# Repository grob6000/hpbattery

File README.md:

# HP Battery

## UPDATED PROJECT

**Please see my new project page at [github.com/calcpsu/cphp82001](https://github.com/calcpsu/cphp82001)**

A Li-Po battery replacement design for HP35/HP45/HP55/HP65/HP67 calculators. The original batteries had ~ 500mAh capacity, while modern Ni-MH replacements are typically ~1500mAh.

While a higher capacity is not necessarily feasible, Li-Po has the advantage of far reduced self-discharge in comparison to Ni-MH, which is an advantage for an intermittently-used device.

Ni-MH / Ni-CD batteries are notorious for leaking, which is somewhat traded-off against the notoriety of Li-Pos to self-immolate.

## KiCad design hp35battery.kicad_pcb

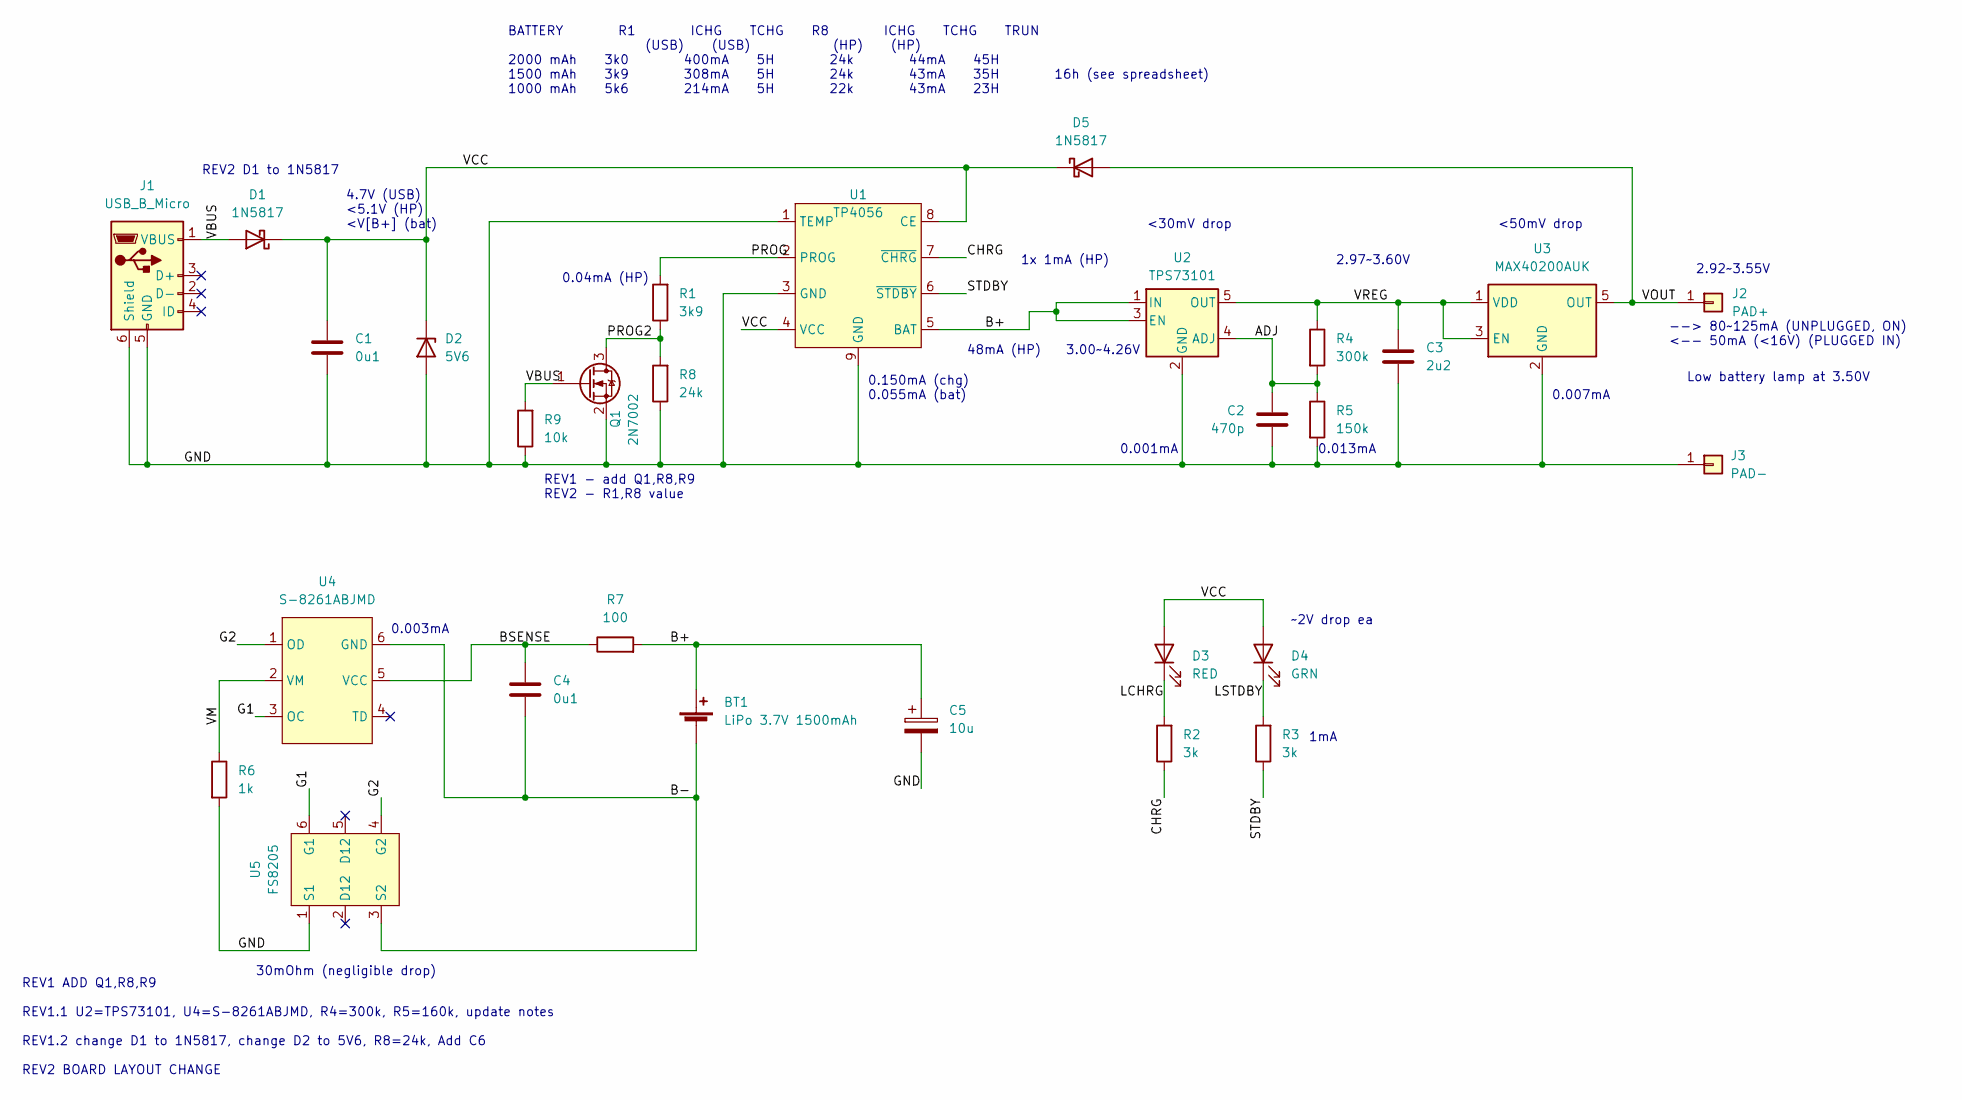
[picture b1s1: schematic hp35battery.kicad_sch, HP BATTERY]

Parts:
BT1: LiPo 3.7V 1500mAh; PinHeader_1x02_P2.00mm_Vertical
C1, C4: 0u1; C_0805_2012Metric
C2: 470p; C_0805_2012Metric
C3: 2u2; C_0805_2012Metric
C5: 10u; C_1210_3225Metric
D1, D5: 1N5817; D_SOD-123
D2: 5V6; D_SMA
D3: RED; LED_0805_2012Metric
D4: GRN; LED_0805_2012Metric
J1: USB_B_Micro; USB_ALIEX_4LEG
J2: PAD+; PAD_10x15
J3: PAD-; PAD_10x15
Q1: 2N7002; SOT-23
R1: 3k9; R_0805_2012Metric
R2, R3: 3k; R_0805_2012Metric
R4: 300k; R_0805_2012Metric
R5: 150k; R_0805_2012Metric
R6: 1k; R_0805_2012Metric
R7: 100; R_0805_2012Metric
R8: 24k; R_0805_2012Metric
R9: 10k; R_0805_2012Metric
U1: TP4056; TI_SO-PowerPAD-8_ThermalVias
U2: TPS73101; SOT-23-5
U3: MAX40200AUK; SOT-23-5
U4: S-8261ABJMD; SOT-23-6
U5: FS8205; SOT-23-6

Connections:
/ADJ: C2.2, R4.2, R5.1, U2.4 (ADJ)
/B+: BT1.1 (+), C5.1, R7.2, U1.5 (BAT), U2.1 (IN), U2.3 (EN)
/B-: BT1.2 (-), C4.2, U4.6 (GND), U5.3 (S2)
/BSENSE: C4.1, R7.1, U4.5 (VCC)
/CHRG: R2.1, U1.7 (~CHRG)
/G1: U4.3 (OC), U5.6 (G1)
/G2: U4.1 (OD), U5.4 (G2)
/GND: C1.2, C2.1, C3.2, C5.2, D2.2 (A), J1.5 (GND), J1.6 (Shield), J3.1, Q1.2 (S), R5.2, R6.2, R8.1, R9.1, U1.1 (TEMP), U1.3 (GND), U1.9 (GND), U2.2 (GND), U3.2 (GND), U5.1 (S1)
/LCHRG: D3.1 (K), R2.2
/LSTDBY: D4.1 (K), R3.2
/PROG: R1.2, U1.2 (PROG)
/PROG2: Q1.3 (D), R1.1, R8.2
/STDBY: R3.1, U1.6 (~STDBY)
/VBUS: D1.2 (A), J1.1 (VBUS), Q1.1 (G), R9.2
/VCC: C1.1, D1.1 (K), D2.1 (K), D3.2 (A), D4.2 (A), D5.1 (K), U1.4 (VCC), U1.8 (CE)
/VM: R6.1, U4.2 (VM)
/VOUT: D5.2 (A), J2.1, U3.5 (OUT)
/VREG: C3.1, R4.1, U2.5 (OUT), U3.1 (VDD), U3.3 (EN)

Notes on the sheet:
3.00~4.26V
BATTERY R1 ICHG TCHG R8 ICHG TCHG TRUN (USB) (USB) (HP) (HP) 2000 mAh 3k0 400mA 5H 24k 44mA 45H 1500 mAh 3k9 308mA 5H 24k 43mA 35H 16h (see spreadsheet) 1000 mAh 5k6 214mA 5H 22k 43mA 23H
--> 80~125mA (UNPLUGGED, ON) <-- 50mA (<16V) (PLUGGED IN)
0.001mA
0.007mA
4.7V (USB) <5.1V (HP) <V[B+] (bat)
2.97~3.60V
0.003mA
~2V drop ea
<30mV drop
1mA
<50mV drop
REV2 D1 to 1N5817
2.92~3.55V
REV1 - add Q1,R8,R9 REV2 - R1,R8 value
0.013mA
48mA (HP)
30mOhm (negligible drop)
0.04mA (HP)
1x 1mA (HP)
0.150mA (chg) 0.055mA (bat)
REV1 ADD Q1,R8,R9 REV1.1 U2=TPS73101, U4=S-8261ABJMD, R4=300k, R5=160k, update notes REV1.2 change D1 to 1N5817, change D2 to 5V6, R8=24k, Add C6 REV2 BOARD LAYOUT CHANGE
Low battery lamp at 3.50V

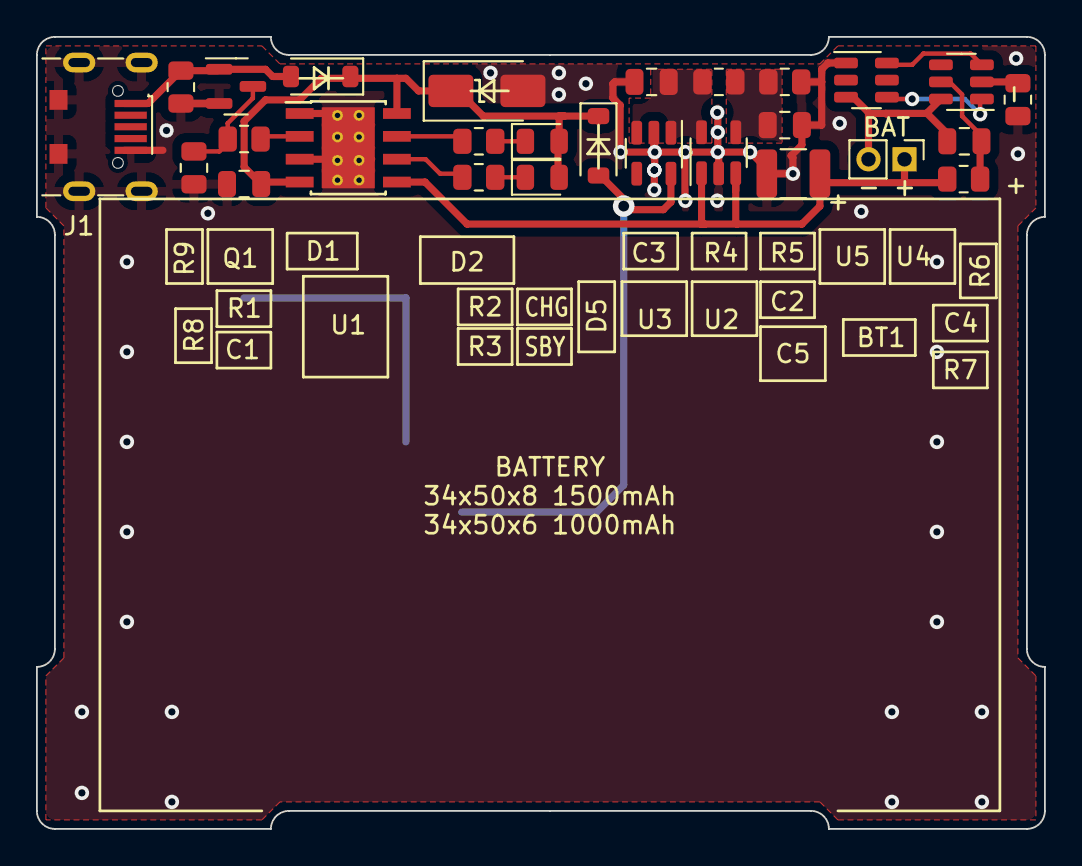
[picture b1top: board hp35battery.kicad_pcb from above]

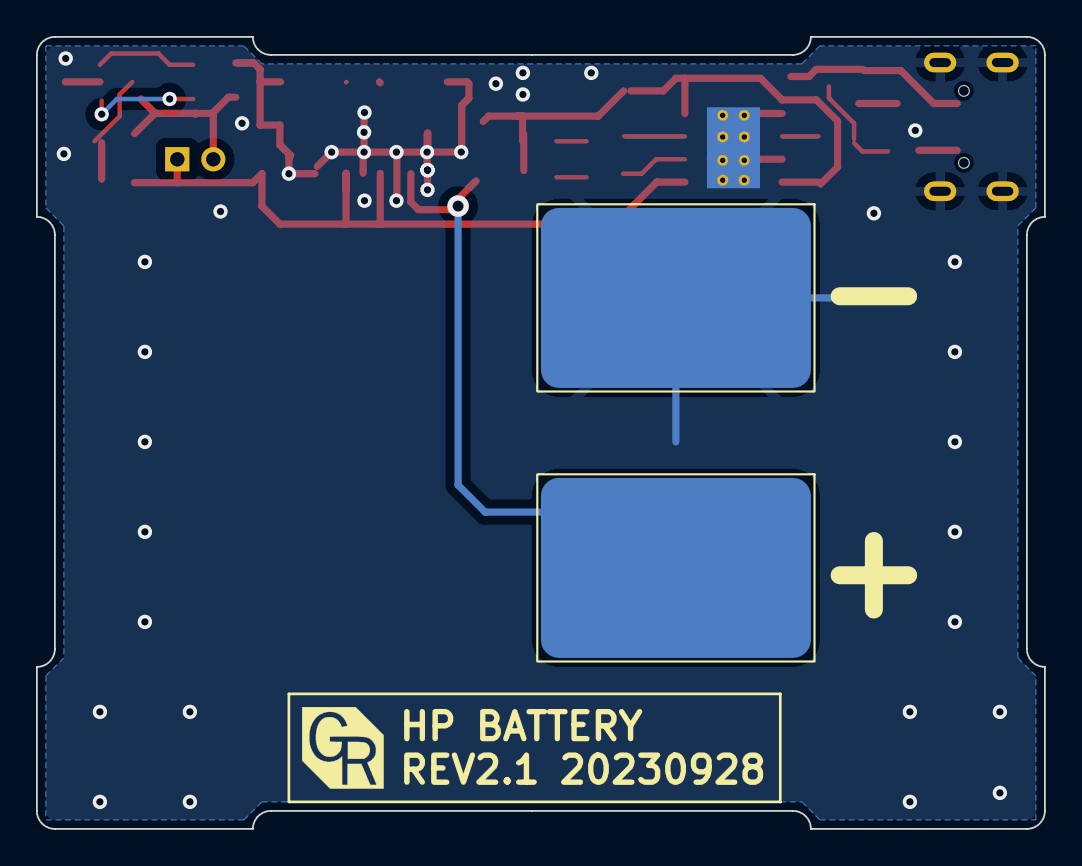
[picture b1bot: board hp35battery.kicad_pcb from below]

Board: 2 copper layers, 56.0 x 44.0 mm, 29 parts (2 on the bottom side), 18 nets.

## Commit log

2023-08-21 Schematic
2023-08-21 Plot Rev0
2023-08-21 Plot Rev1
2023-08-21 Calculation
2023-08-21 Discharge curves
2023-08-21 Calc updates
2023-08-21 Further calc and schematic update
2023-08-21 Schematic plot
2023-08-21 Create block diagram
2023-10-05 Rev 2.1
    Updated to:
    * Fit HP67 (reduced length/width, contact size/position)
    * Board shape has 1mm recess on all four sides (better case design)
    * All components fit on top side
    * V2.1: slightly better thermal arrangement for regulator
2023-12-12 Add photos
